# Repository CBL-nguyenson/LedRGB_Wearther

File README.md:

# MakerLab Openweather RGB

## Remake by Nguyenson

## Tổng quan

    Bối cảnh nhân vật: 
    Xuất phát từ tình yêu thiên nhiên tươi đẹp của thành phố Đà Lạt và nhằm tạo sân chơi phát triển toàn diện cho sinh viên, các giảng viên yêu nghề của Khoa Kiến trúc ĐH Yersin Đà Lạt đã phối hợp cùng Mekongaholics trong khuôn khổ lễ hội "Nổ Cái Bùm" kiến tạo một tác phẩm tượng rối khổng lồ biểu trưng cho nhân vật giả tưởng là vị thần rừng bảo hộ cho sự phát triển bền vững và nhân văn của thành phố cao nguyên. 
Mỗi năm, diện mạo của con rối sẽ điều chỉnh thay đổi để cập nhật cho phù hợp với nhu cầu thực tế về truyền thông giáo dục môi trường.  Rối có các chức năng trưng bày và biểu diễn phục vụ giải trí và truyền thông giáo dục nhận thức môi trường trong khuôn khổ lễ hội Nổ Cái Bùm cũng như các sự kiện tương tự: lễ hội kể chuyện cho trẻ em, lễ hội hoa, ngày khoa học kĩ thuật quốc gia...
Khả năng vận hành dự kiến: 
- Tham gia các triển lãm nghệ thuật đương đại dạng tác phẩm thị giác kết hợp đèn led, chiếu phim & âm nhạc
- Trưng bày phục vụ giáo dục sáng tạo: mô phỏng cấu trúc cơ học dạng đứng có bệ đỡ và hệ thống dây kéo cử động cho con rối
- Di chuyển: đi bộ, vẫy tay, làm tư thế chụp ảnh dễ thương, cầm nắm đồ vật, gật đầu, lắc đầu, cúi người chào, lắc hông, ngồi xổm, nhún nhảy theo nhạc... 
- Tương tác trực tiếp với khán giả qua cử động bắt tay và trao nhận vật phẩm...
Phác thảo ý tưởng: Mekongaholics & Ban tổ chức lễ hội Nổ Cái Bùm
Bản vẽ kĩ thuật: Khoa Kiến trúc ĐH Yersin Đà Lạt
Thực hiện thi công cơ khí: Giảng viên Khoa Kiến trúc ĐH Yersin Đà Lạt

---------------------------------------------------

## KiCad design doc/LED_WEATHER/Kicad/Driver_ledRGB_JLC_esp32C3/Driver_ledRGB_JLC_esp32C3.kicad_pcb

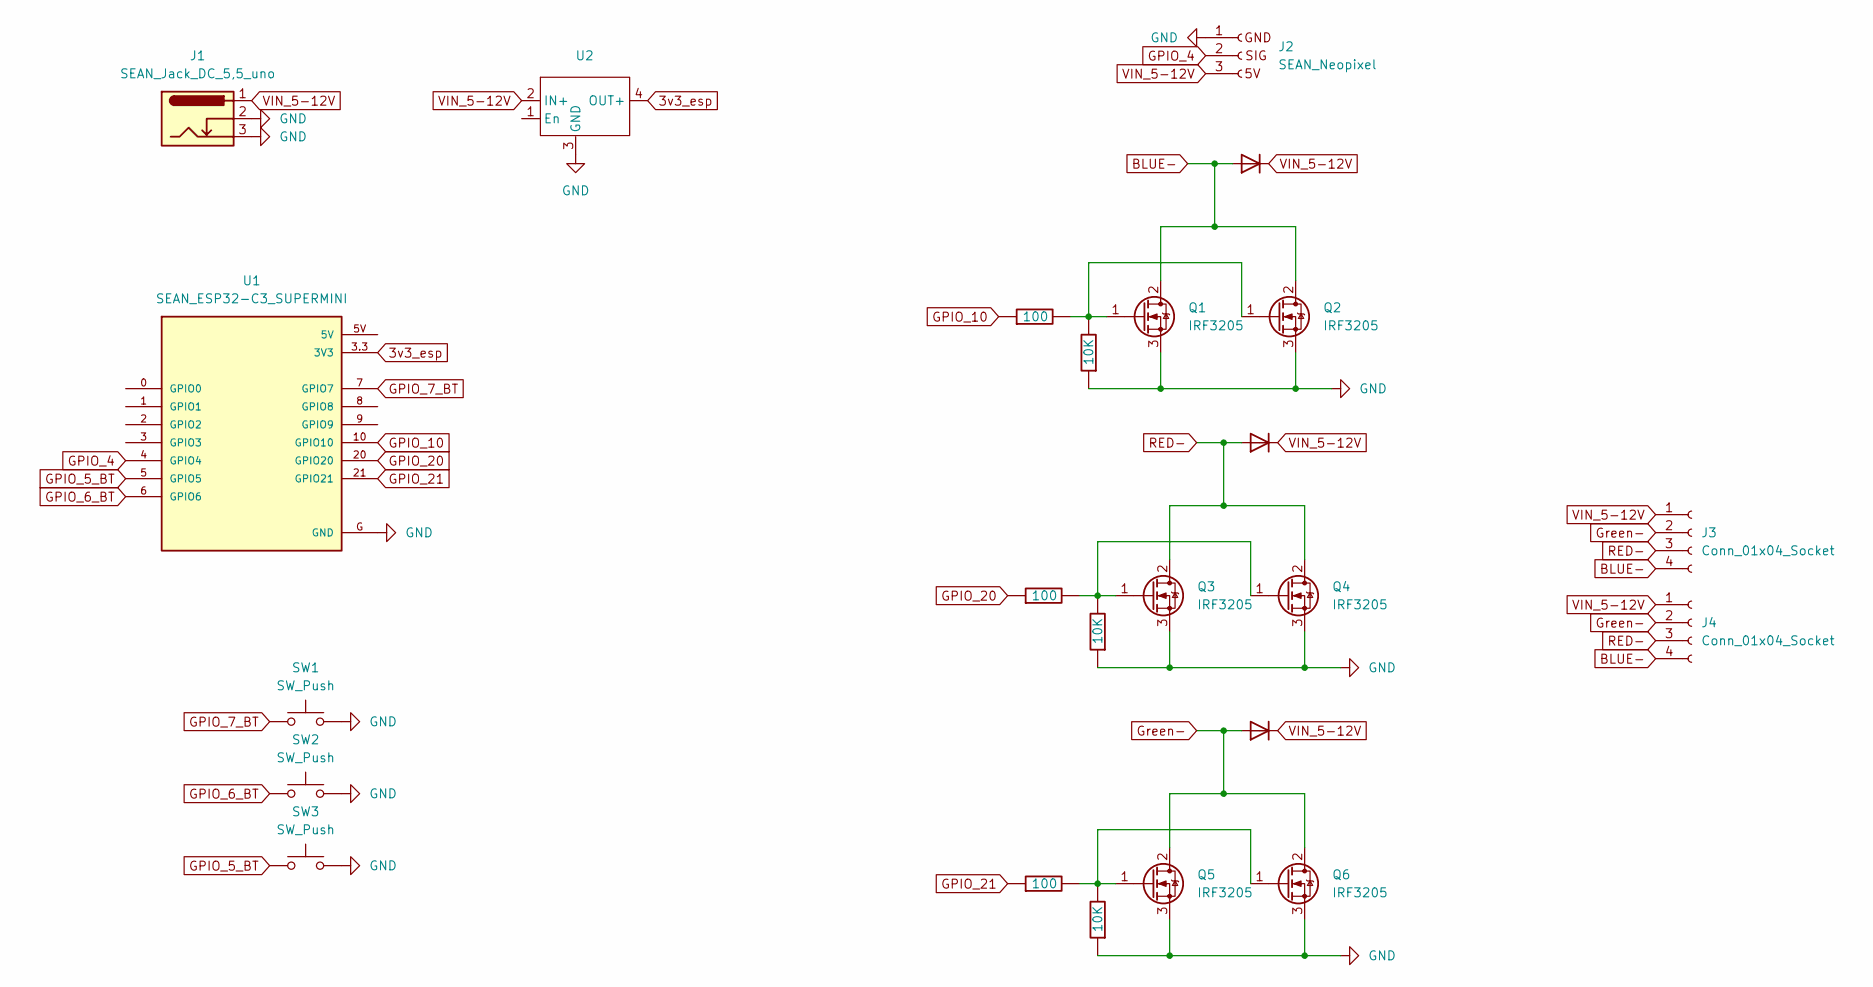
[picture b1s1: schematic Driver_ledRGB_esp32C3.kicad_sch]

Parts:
D1, D2, D3: SEAN_D; D_DO-35_SOD27_P7.62mm_Horizontal
J1: SEAN_Jack_DC_5,5_uno; SEAN_Jack_DC_5,5_uno_
J2: SEAN_Neopixel
J3, J4: Conn_01x04_Socket; PinHeader_1x04_P2.54mm_Vertical
Q1, Q2, Q3, Q4, Q5, Q6: IRF3205; TO-220-3_Horizontal_TabUp
R1, R4, R6: 10K; R_Axial_DIN0207_L6.3mm_D2.5mm_P7.62mm_Horizontal
R2, R3, R5: 100; R_Axial_DIN0207_L6.3mm_D2.5mm_P7.62mm_Horizontal
SW1, SW2, SW3: SW_Push; SW_PUSH-12mm
U1: SEAN_ESP32-C3_SUPERMINI; SEAN_ESP32-C3_SUPERMINI_hold
U2: SEAN_BUCK_Mini_3A_V2

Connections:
3v3_esp: U1.3.3 (3V3), U2.4 (OUT+)
BLUE-: D1.2 (A), J3.4, J4.4, Q1.2 (D), Q2.2 (D)
GND: J1.2, J1.3, J2.1 (GND), Q1.3 (S), Q2.3 (S), Q3.3 (S), Q4.3 (S), Q5.3 (S), Q6.3 (S), R1.1, R4.1, R6.1, SW1.2, SW2.2, SW3.2, U1.G (GND), U2.3 (GND)
GPIO_4: J2.2 (5V), U1.4 (GPIO4)
GPIO_5_BT: SW3.1, U1.5 (GPIO5)
GPIO_6_BT: SW2.1, U1.6 (GPIO6)
GPIO_7_BT: SW1.1, U1.7 (GPIO7)
GPIO_10: R2.1, U1.10 (GPIO10)
GPIO_20: R3.1, U1.20 (GPIO20)
GPIO_21: R5.1, U1.21 (GPIO21)
Green-: D3.2 (A), J3.2, J4.2, Q5.2 (D), Q6.2 (D)
unnamed: Q1.1 (G), Q2.1 (G), R1.2, R2.2
unnamed: Q3.1 (G), Q4.1 (G), R3.2, R4.2
unnamed: Q5.1 (G), Q6.1 (G), R5.2, R6.2
RED-: D2.2 (A), J3.3, J4.3, Q3.2 (D), Q4.2 (D)
VIN_5-12V: D1.1 (K), D2.1 (K), D3.1 (K), J1.1, J2.3 (SDA), J3.1, J4.1, U2.2 (IN+)

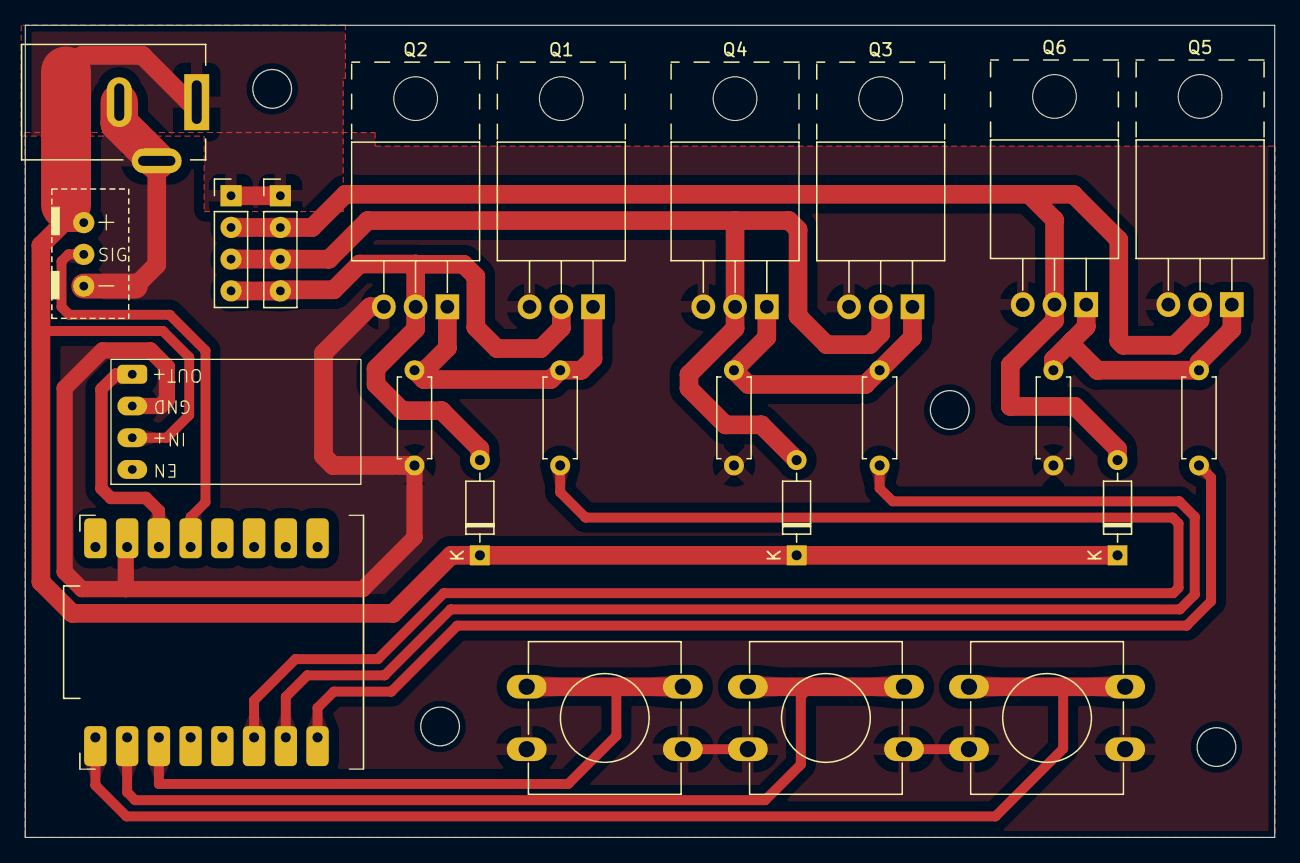
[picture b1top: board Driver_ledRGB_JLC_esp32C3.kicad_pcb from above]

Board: 2 copper layers, 100.0 x 65.0 mm, 24 parts (0 on the bottom side), 16 nets.

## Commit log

2024-08-11 Code_V2
2024-08-29 enum
